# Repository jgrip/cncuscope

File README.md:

# Microscope CNC Controller

### Overview

Six axis CNC controller for a microscope, running [FluidNC](https://github.com/bdring/FluidNC).

This is based on Bart Drings excellent [6-pack CNC controller](https://github.com/bdring/6-Pack_CNC_Controller).

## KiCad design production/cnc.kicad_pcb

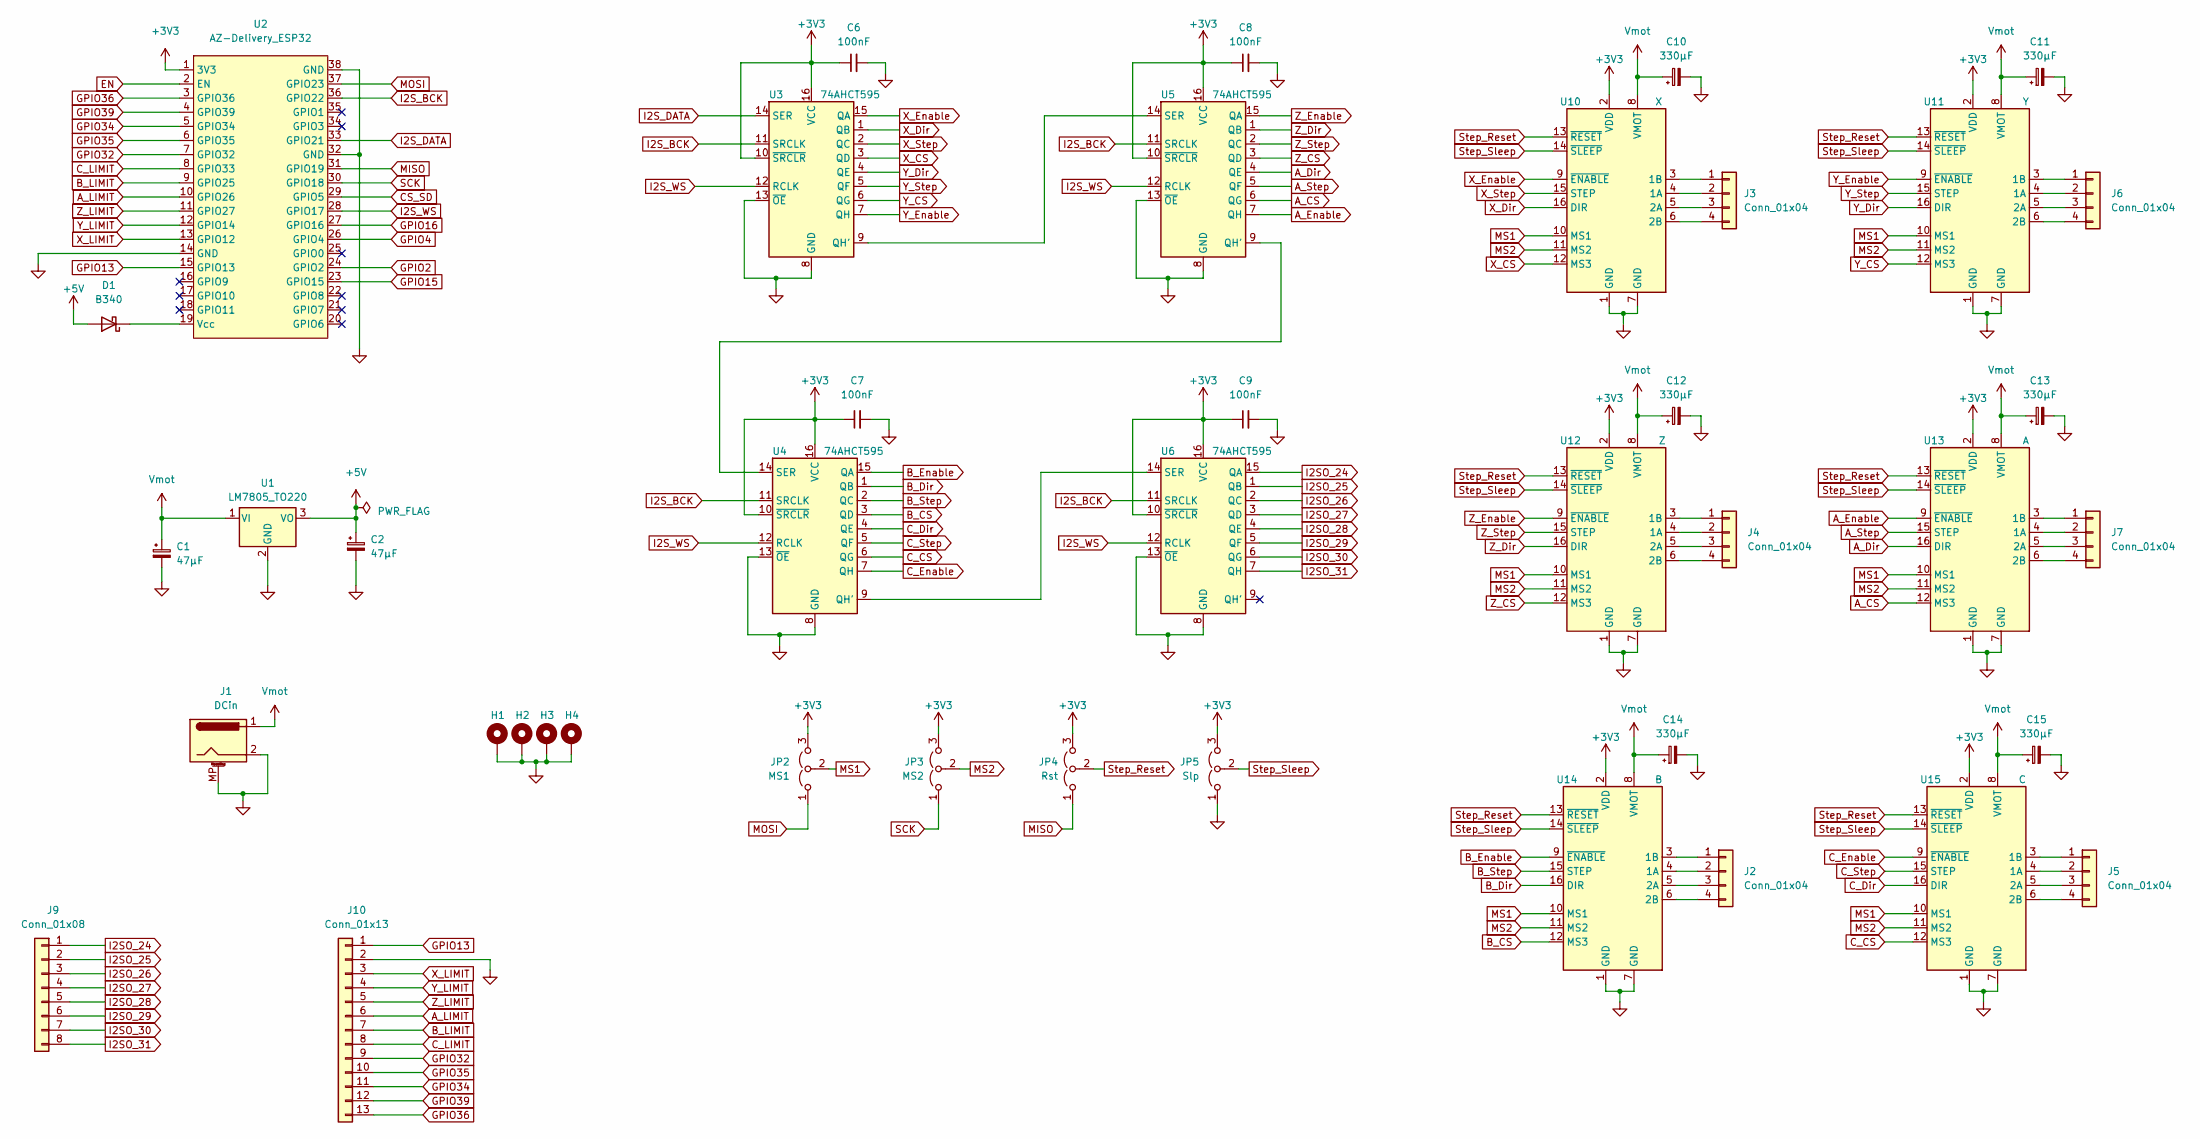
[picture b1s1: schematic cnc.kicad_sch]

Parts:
C1, C2: 47µF; CP_Elec_6.3x5.4_Nichicon
C6, C7, C8, C9: 100nF; C_0805_2012Metric
C10, C11, C12, C13, C14, C15: 330µF; CP_Elec_10x10.5
D1: B340; D_SMC
H1, H2, H3, H4: MountingHole_Pad; MountingHole_3.2mm_M3_DIN965_Pad
J1: DCin; BarrelJack_Wuerth_6941xx301002
J2, J3, J4, J5, J6, J7: Conn_01x04; JST_XH_B4B-XH-A_1x04_P2.50mm_Vertical
J9: Conn_01x08; PinHeader_1x08_P2.54mm_Vertical
J10: Conn_01x13; PinHeader_1x13_P2.54mm_Vertical
JP2: MS1; PinHeader_1x03_P2.54mm_Vertical
JP3: MS2; PinHeader_1x03_P2.54mm_Vertical
JP4: Rst; PinHeader_1x03_P2.54mm_Vertical
JP5: Slp; PinHeader_1x03_P2.54mm_Vertical
U1: LM7805_TO220; TO-220-3_Vertical
U2: AZ-Delivery_ESP32; ESP32-module
U3, U4, U5, U6: 74AHCT595; SOIC-16_3.9x9.9mm_P1.27mm
U10: X; Pololu_Breakout-16_15.2x20.3mm
U11: Y; Pololu_Breakout-16_15.2x20.3mm
U12: Z; Pololu_Breakout-16_15.2x20.3mm
U13: A; Pololu_Breakout-16_15.2x20.3mm
U14: B; Pololu_Breakout-16_15.2x20.3mm
U15: C; Pololu_Breakout-16_15.2x20.3mm

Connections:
+3V3: C6.1, C7.1, C8.1, C9.1, JP2.3 (B), JP3.3 (B), JP4.3 (B), JP5.3 (B), U2.1 (3V3), U3.10 (~SRCLR), U3.16 (VCC), U4.10 (~SRCLR), U4.16 (VCC), U5.10 (~SRCLR), U5.16 (VCC), U6.10 (~SRCLR), U6.16 (VCC), U10.2 (VDD), U11.2 (VDD), U12.2 (VDD), U13.2 (VDD), U14.2 (VDD), U15.2 (VDD)
+5V: C2.1, D1.2 (A), U1.3 (VO)
A_CS: U5.6 (QG), U13.12 (MS3)
A_Dir: U5.4 (QE), U13.16 (DIR)
A_Enable: U5.7 (QH), U13.9 (~ENABLE)
A_LIMIT: J10.6, U2.10 (GPIO26)
A_Step: U5.5 (QF), U13.15 (STEP)
B_CS: U4.3 (QD), U14.12 (MS3)
B_Dir: U4.1 (QB), U14.16 (DIR)
B_Enable: U4.15 (QA), U14.9 (~ENABLE)
B_LIMIT: J10.7, U2.9 (GPIO25)
B_Step: U4.2 (QC), U14.15 (STEP)
CS_SD: U2.29 (GPIO5)
C_CS: U4.6 (QG), U15.12 (MS3)
C_Dir: U4.4 (QE), U15.16 (DIR)
C_Enable: U4.7 (QH), U15.9 (~ENABLE)
C_LIMIT: J10.8, U2.8 (GPIO33)
C_Step: U4.5 (QF), U15.15 (STEP)
EN: U2.2 (EN)
GND: C1.2, C2.2, C6.2, C7.2, C8.2, C9.2, C10.2, C11.2, C12.2, C13.2, C14.2, C15.2, H1.1, H2.1, H3.1, H4.1, J1.2, J1.MP (MountPin), J10.2, JP5.1 (A), U1.2 (GND), U2.14 (GND), U2.32 (GND), U2.38 (GND), U3.8 (GND), U3.13 (~OE), U4.8 (GND), U4.13 (~OE), U5.8 (GND), U5.13 (~OE), U6.8 (GND), U6.13 (~OE), U10.1 (GND), U10.7 (GND), U11.1 (GND), U11.7 (GND), U12.1 (GND), U12.7 (GND), U13.1 (GND), U13.7 (GND), U14.1 (GND), U14.7 (GND), U15.1 (GND), U15.7 (GND)
GPIO2: U2.24 (GPIO2)
GPIO4: U2.26 (GPIO4)
GPIO13: J10.1, U2.15 (GPIO13)
GPIO15: U2.23 (GPIO15)
GPIO16: U2.27 (GPIO16)
GPIO32: J10.9, U2.7 (GPIO32)
GPIO34: J10.11, U2.5 (GPIO34)
GPIO35: J10.10, U2.6 (GPIO35)
GPIO36: J10.13, U2.3 (GPIO36)
GPIO39: J10.12, U2.4 (GPIO39)
I2SO_24: J9.1, U6.15 (QA)
I2SO_25: J9.2, U6.1 (QB)
I2SO_26: J9.3, U6.2 (QC)
I2SO_27: J9.4, U6.3 (QD)
I2SO_28: J9.5, U6.4 (QE)
I2SO_29: J9.6, U6.5 (QF)
I2SO_30: J9.7, U6.6 (QG)
I2SO_31: J9.8, U6.7 (QH)
I2S_BCK: U2.36 (GPIO22), U3.11 (SRCLK), U4.11 (SRCLK), U5.11 (SRCLK), U6.11 (SRCLK)
I2S_DATA: U2.33 (GPIO21), U3.14 (SER)
I2S_WS: U2.28 (GPIO17), U3.12 (RCLK), U4.12 (RCLK), U5.12 (RCLK), U6.12 (RCLK)
MISO: JP4.1 (A), U2.31 (GPIO19)
MOSI: JP2.1 (A), U2.37 (GPIO23)
MS1: JP2.2 (C), U10.10 (MS1), U11.10 (MS1), U12.10 (MS1), U13.10 (MS1), U14.10 (MS1), U15.10 (MS1)
MS2: JP3.2 (C), U10.11 (MS2), U11.11 (MS2), U12.11 (MS2), U13.11 (MS2), U14.11 (MS2), U15.11 (MS2)
unnamed: D1.1 (K), U2.19 (Vcc)
unnamed: J2.1, U14.3 (1B)
unnamed: J2.2, U14.4 (1A)
unnamed: J2.3, U14.5 (2A)
unnamed: J2.4, U14.6 (2B)
unnamed: J3.1, U10.3 (1B)
unnamed: J3.2, U10.4 (1A)
unnamed: J3.3, U10.5 (2A)
unnamed: J3.4, U10.6 (2B)
unnamed: J4.1, U12.3 (1B)
unnamed: J4.2, U12.4 (1A)
unnamed: J4.3, U12.5 (2A)
unnamed: J4.4, U12.6 (2B)
unnamed: J5.1, U15.3 (1B)
unnamed: J5.2, U15.4 (1A)
unnamed: J5.3, U15.5 (2A)
unnamed: J5.4, U15.6 (2B)
unnamed: J6.1, U11.3 (1B)
unnamed: J6.2, U11.4 (1A)
unnamed: J6.3, U11.5 (2A)
unnamed: J6.4, U11.6 (2B)
unnamed: J7.1, U13.3 (1B)
unnamed: J7.2, U13.4 (1A)
unnamed: J7.3, U13.5 (2A)
unnamed: J7.4, U13.6 (2B)
unnamed: U3.9 (QH'), U5.14 (SER)
unnamed: U4.9 (QH'), U6.14 (SER)
unnamed: U4.14 (SER), U5.9 (QH')
SCK: JP3.1 (A), U2.30 (GPIO18)
Step_Reset: JP4.2 (C), U10.13 (~RESET), U11.13 (~RESET), U12.13 (~RESET), U13.13 (~RESET), U14.13 (~RESET), U15.13 (~RESET)
Step_Sleep: JP5.2 (C), U10.14 (~SLEEP), U11.14 (~SLEEP), U12.14 (~SLEEP), U13.14 (~SLEEP), U14.14 (~SLEEP), U15.14 (~SLEEP)
Vmot: C1.1, C10.1, C11.1, C12.1, C13.1, C14.1, C15.1, J1.1, U1.1 (VI), U10.8 (VMOT), U11.8 (VMOT), U12.8 (VMOT), U13.8 (VMOT), U14.8 (VMOT), U15.8 (VMOT)
X_CS: U3.3 (QD), U10.12 (MS3)
X_Dir: U3.1 (QB), U10.16 (DIR)
X_Enable: U3.15 (QA), U10.9 (~ENABLE)
X_LIMIT: J10.3, U2.13 (GPIO12)
X_Step: U3.2 (QC), U10.15 (STEP)
Y_CS: U3.6 (QG), U11.12 (MS3)
Y_Dir: U3.4 (QE), U11.16 (DIR)
Y_Enable: U3.7 (QH), U11.9 (~ENABLE)
Y_LIMIT: J10.4, U2.12 (GPIO14)
Y_Step: U3.5 (QF), U11.15 (STEP)
Z_CS: U5.3 (QD), U12.12 (MS3)
Z_Dir: U5.1 (QB), U12.16 (DIR)
Z_Enable: U5.15 (QA), U12.9 (~ENABLE)
Z_LIMIT: J10.5, U2.11 (GPIO27)
Z_Step: U5.2 (QC), U12.15 (STEP)

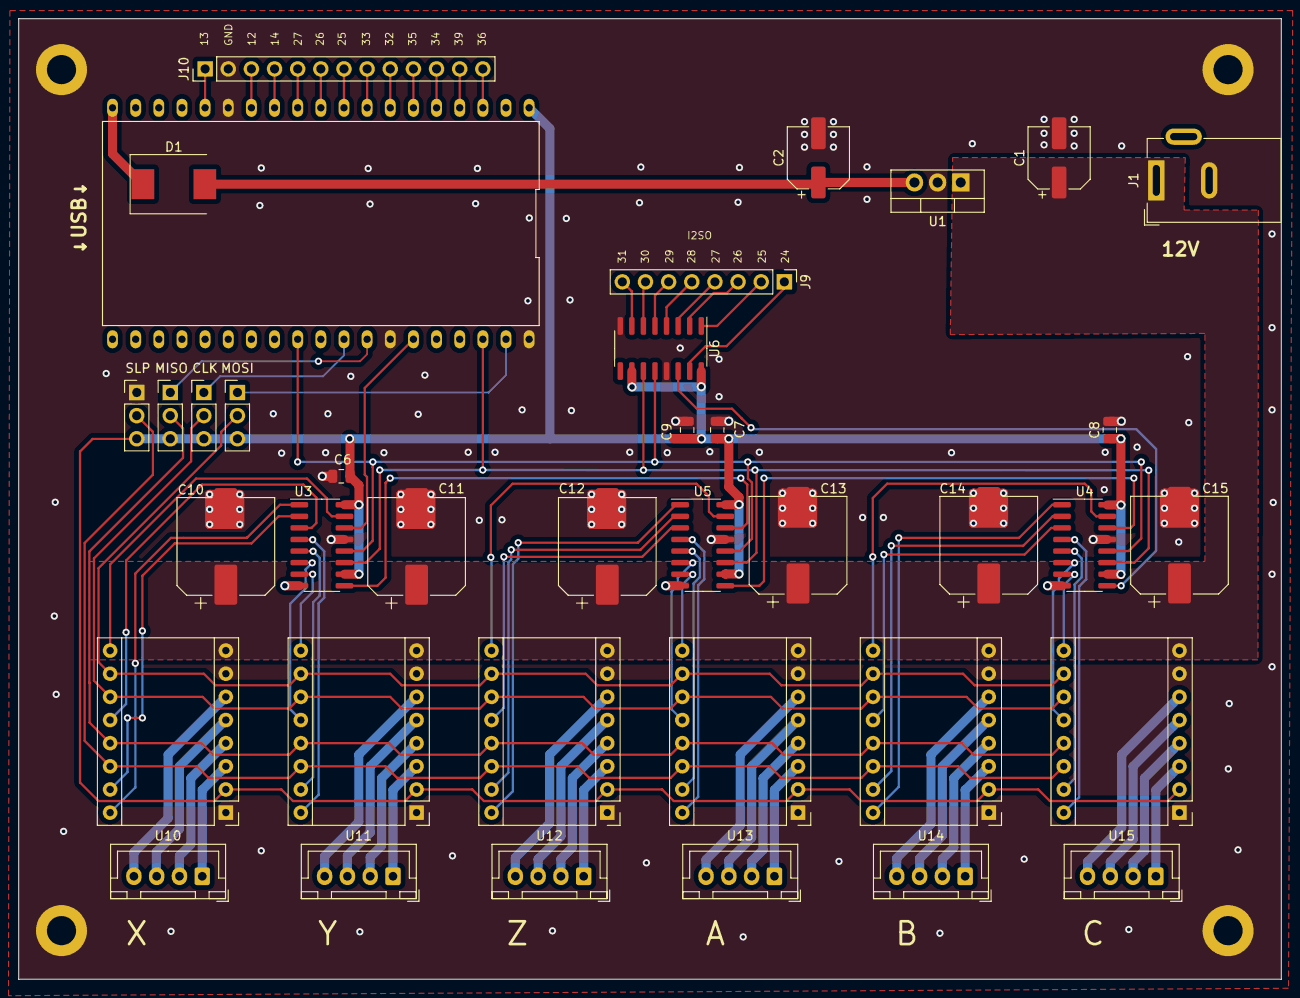
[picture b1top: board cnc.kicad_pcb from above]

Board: 2 copper layers, 138.6 x 105.4 mm, 42 parts (0 on the bottom side), 86 nets.

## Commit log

2021-07-10 Initial revision
2022-05-11 Cleanup
2022-05-11 Readme and license
2023-04-18 Add gitignore
2023-04-18 New revision
2023-04-18 Remove temporary files
2023-04-18 Add gerbers
